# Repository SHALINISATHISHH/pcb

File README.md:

View this project on [CADLAB.io](https://cadlab.io/project/29144). 

# pcb

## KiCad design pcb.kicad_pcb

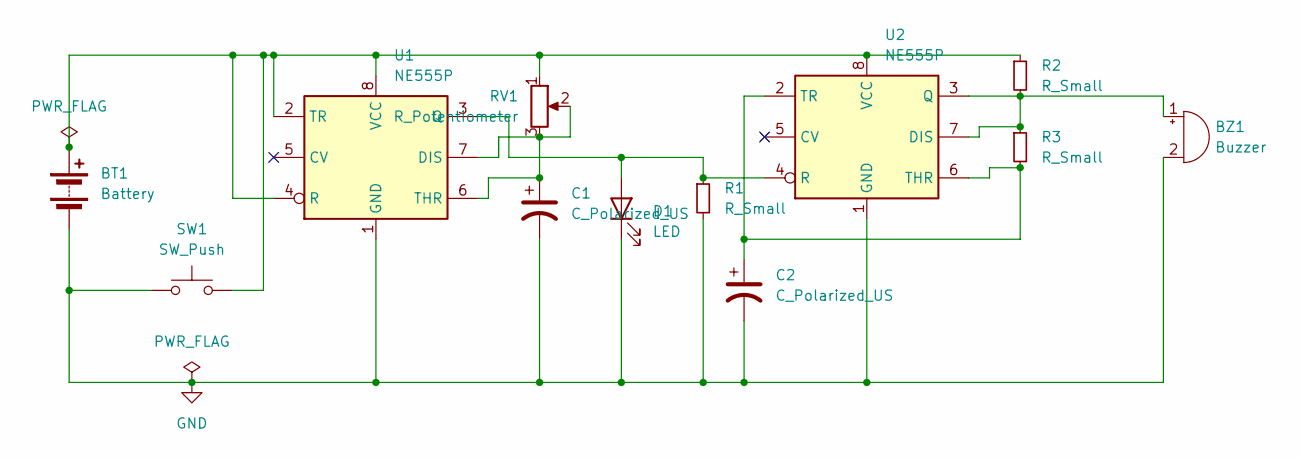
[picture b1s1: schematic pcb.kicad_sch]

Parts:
BT1: Battery; BatteryHolder_Bulgin_BX0036_1xC
BZ1: Buzzer; Buzzer_15x7.5RM7.6
C1, C2: C_Polarized_US; CP_Elec_3x5.3
D1: LED; LED_0402_1005Metric_Pad0.77x0.64mm_HandSolder
R1, R2, R3: R_Small; R_LDR_4.9x4.2mm_P2.54mm_Vertical
RV1: R_Potentiometer; Potentiometer_ACP_CA6-VSMD_Vertical
SW1: SW_Push; MagneticBuzzer_CUI_CST-931RP-A
U1, U2: NE555P; DIP-8-16_W7.62mm

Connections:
GND: BT1.2 (-), BZ1.2 (-), C1.2, C2.2, D1.1 (K), R1.2, SW1.1, U1.1 (GND), U2.1 (GND)
unnamed: BT1.1 (+), R2.1, RV1.1, SW1.2, U1.2 (TR), U1.4 (R), U1.8 (VCC), U2.8 (VCC)
unnamed: BZ1.1 (+), R2.2, R3.1, U2.3 (Q), U2.7 (DIS)
unnamed: D1.2 (A), R1.1, U1.3 (Q), U2.4 (R)
unnamed: C1.1, RV1.2, RV1.3, U1.6 (THR), U1.7 (DIS)
unnamed: C2.1, R3.2, U2.2 (TR), U2.6 (THR)

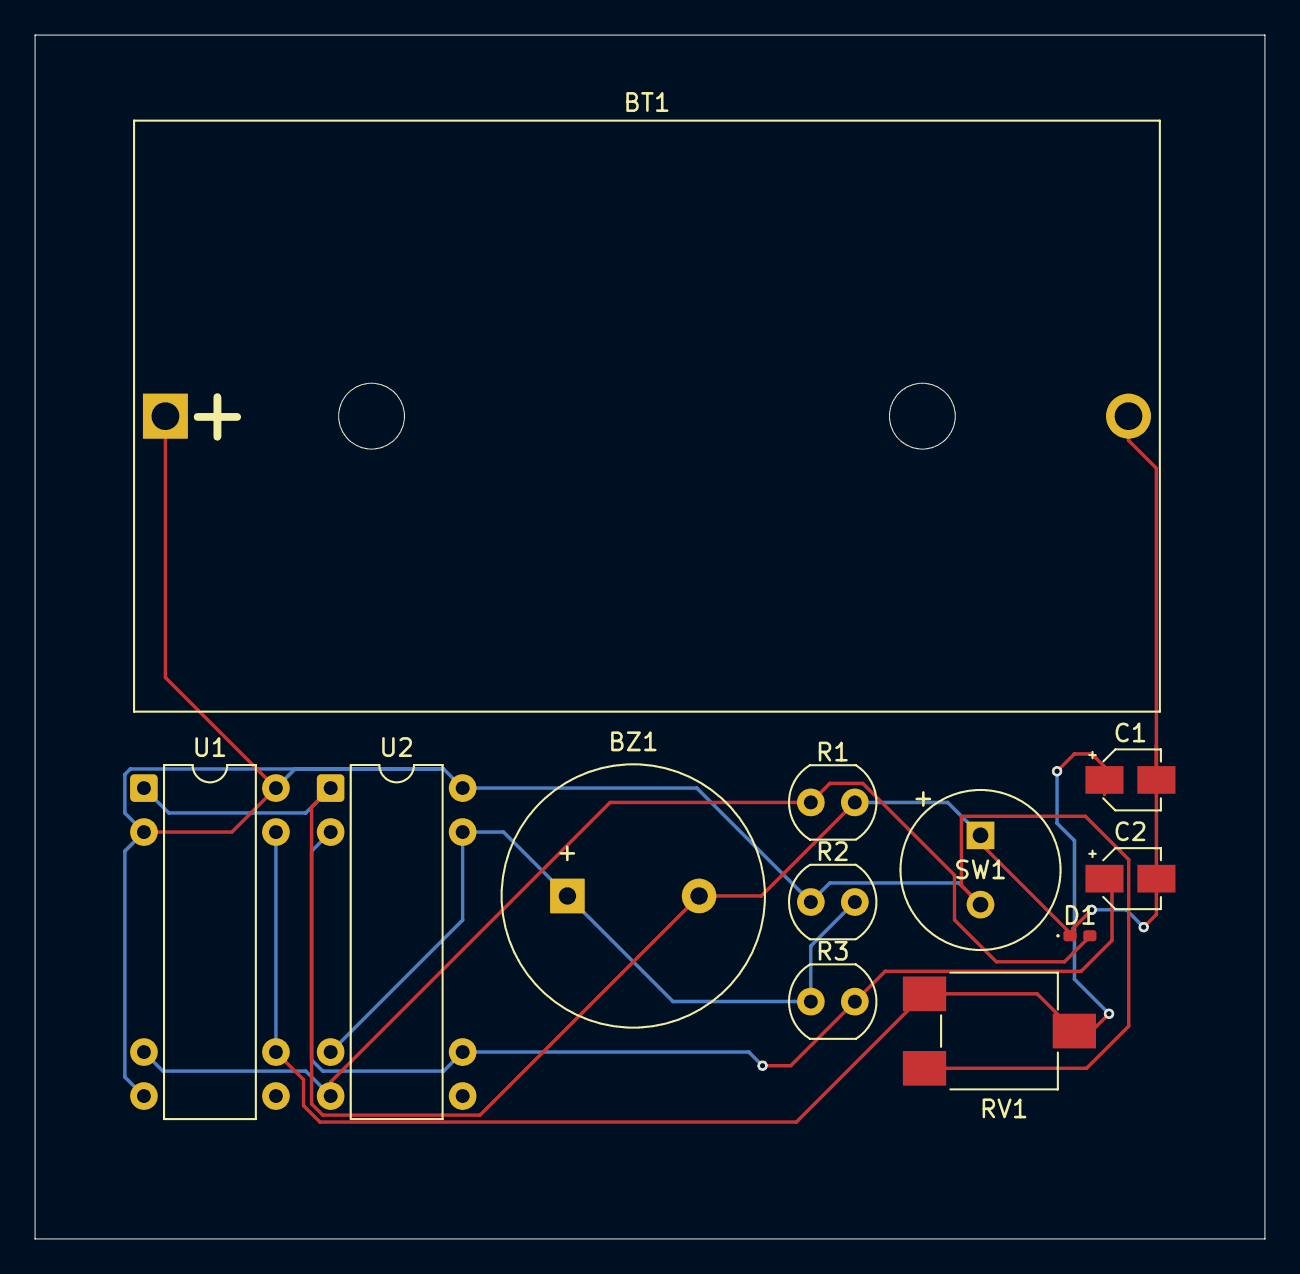
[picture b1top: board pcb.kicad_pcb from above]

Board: 2 copper layers, 71.0 x 69.5 mm, 12 parts (0 on the bottom side), 6 nets.

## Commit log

2025-04-02 Backlink to CADLAB.io has been added.
2025-04-02 updated Design
2025-04-03 PCB_design
